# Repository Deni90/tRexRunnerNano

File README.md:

# Welcome to tRexRunnerNano Project

## About
This project tries to be the smallest implementation of Google's easter egg T-Rex Runner with resolution of only 128x32px.

The goal is to make a small game console by using WCH CH32V003 microcontroller and SSSD1306 oled display.

## Schematic  & PCB
Made with KiCAD 10

## Firmware

Firmware is written in C using **ch32fun**, an open source development environment for the CH32V003.

WCH CH-Link is used for flashing the firmware

### Building and flashing

```
make
```

## DM DIY-MORE OLED-091
Popular I2C OLED 32x128 display from diy-more has an issue. It doesn't properly start after power on, but starts without problems after reset.
To solve this problem swap R3 and R4 resistors.

Solution found at:
https://youtu.be/__3InV5tdzM

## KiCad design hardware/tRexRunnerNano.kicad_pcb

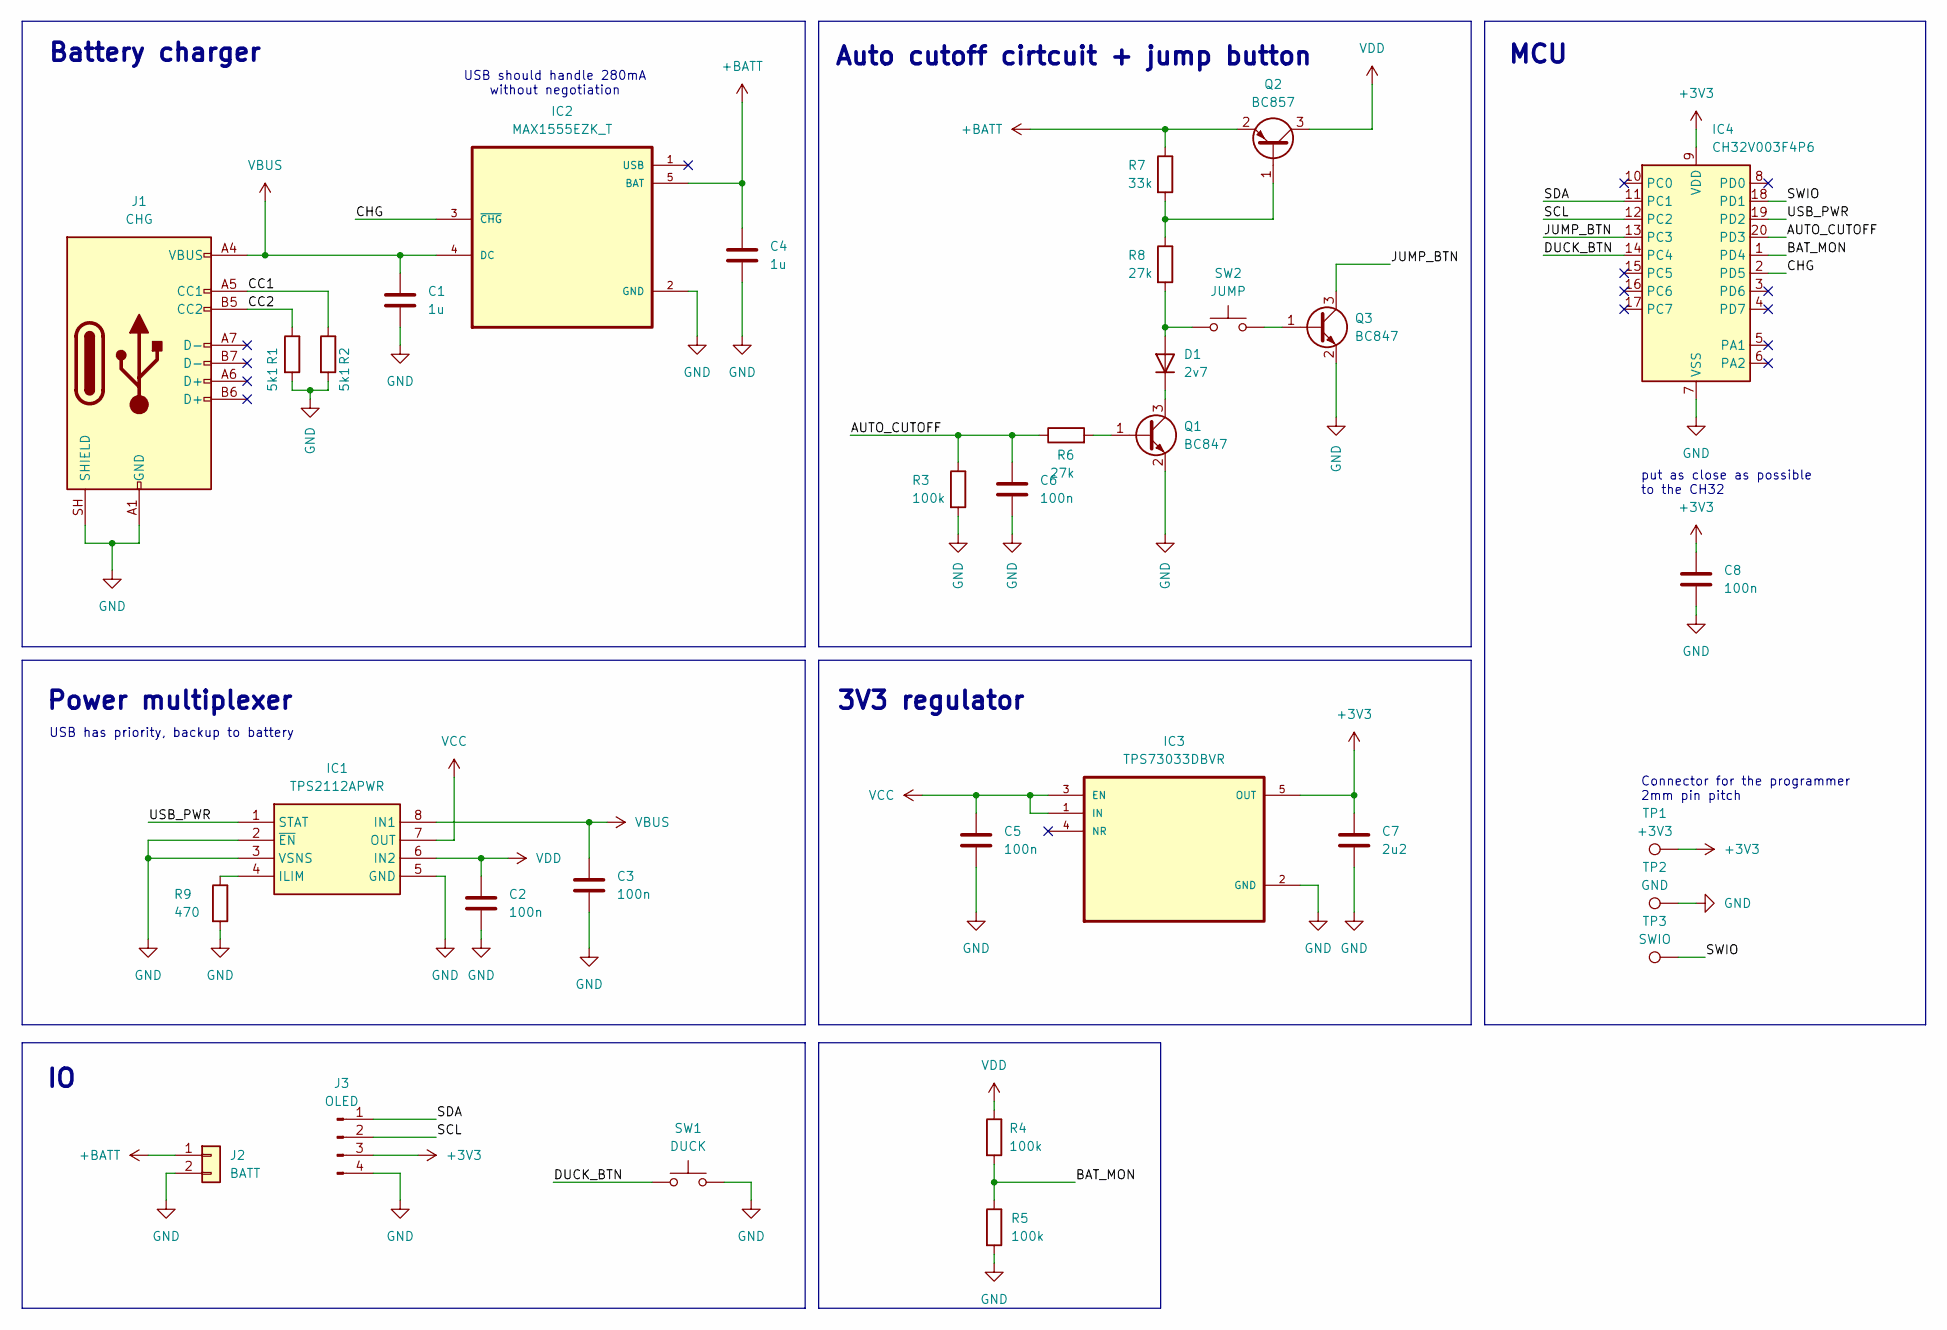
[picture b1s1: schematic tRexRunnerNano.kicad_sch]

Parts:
C1, C4: 1u; C_0603_1608Metric
C2, C3, C5, C6, C8: 100n; C_0603_1608Metric
C7: 2u2; C_0603_1608Metric
D1: 2v7; D_MiniMELF
IC1: TPS2112APWR; SOP65P640X120-8N; Mouser Part Number 595-TPS2112APWR
IC2: MAX1555EZK_T; SOT95P275X110-5N
IC3: TPS73033DBVR; SOT95P280X145-5N
IC4: CH32V003F4P6; TSSOP-20_4.4x6.5mm_P0.65mm
J1: CHG; USB_C_Receptacle_GCT_USB4105-xx-A_16P_TopMnt_Horizontal
J2: BATT; JST_GH_SM02B-GHS-TB_1x02-1MP_P1.25mm_Horizontal
J3: OLED; PinHeader_1x04_P2.54mm_Vertical
Q1, Q3: BC847; SOT-23
Q2: BC857; SOT-23
R1, R2: 5k1; R_0603_1608Metric
R3, R4, R5: 100k; R_0603_1608Metric
R6, R8: 27k; R_0603_1608Metric
R7: 33k; R_0603_1608Metric
R9: 470; R_0603_1608Metric
SW1: DUCK; SW_PUSH_6mm
SW2: JUMP; SW_PUSH_6mm
TP1: +3V3; TestPoint_Pad_D1.0mm
TP2: GND; TestPoint_Pad_D1.0mm
TP3: SWIO; TestPoint_Pad_D1.0mm

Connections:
+3V3: C7.1, C8.1, IC3.5 (OUT), IC4.9 (VDD), J3.3, TP1.1 (1_1)
+BATT: C4.1, IC2.5 (BAT), J2.1, Q2.2 (E), R7.1
/AUTO_CUTOFF: C6.1, IC4.20 (PD3), R3.1, R6.1
/BAT_MON: IC4.1 (PD4), R4.2, R5.1
/CC1: J1.A5 (CC1), R2.1
/CC2: J1.B5 (CC2), R1.1
/CHG: IC2.3 (~CHG), IC4.2 (PD5)
/DUCK_BTN: IC4.14 (PC4), SW1.1
/JUMP_BTN: IC4.13 (PC3), Q3.3 (C)
/SCL: IC4.12 (PC2), J3.2
/SDA: IC4.11 (PC1), J3.1
/SWIO: IC4.18 (PD1), TP3.1 (1_1)
/USB_PWR: IC1.1 (STAT), IC4.19 (PD2)
GND: C1.2, C2.2, C3.2, C4.2, C5.2, C6.2, C7.2, C8.2, IC1.2 (~EN), IC1.3 (VSNS), IC1.5 (GND), IC2.2 (GND), IC3.2 (GND), IC4.7 (VSS), J1.A1 (GND), J1.A12 (GND), J1.B1 (GND), J1.B12 (GND), J1.SH (SHIELD), J2.2, J3.4, Q1.2 (E), Q3.2 (E), R1.2, R2.2, R3.2, R5.2, R9.2, SW1.2, TP2.1 (1_1)
unnamed: D1.2 (A), R8.2, SW2.1
unnamed: D1.1 (K), Q1.3 (C)
unnamed: IC1.4 (ILIM), R9.1
unnamed: Q1.1 (B), R6.2
unnamed: Q2.1 (B), R7.2, R8.1
unnamed: Q3.1 (B), SW2.2
VBUS: C1.1, C3.1, IC1.8 (IN1), IC2.4 (DC), J1.A4 (VBUS), J1.A9 (VBUS), J1.B4 (VBUS), J1.B9 (VBUS)
VCC: C5.1, IC1.7 (OUT), IC3.1 (IN), IC3.3 (EN)
VDD: C2.1, IC1.6 (IN2), Q2.3 (C), R4.1

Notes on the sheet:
Power multiplexer
put as close as possible to the CH32
Connector for the programmer 2mm pin pitch
Battery charger
USB has priority, backup to battery
USB should handle 280mA without negotiation
Auto cutoff cirtcuit + jump button
MCU
3V3 regulator

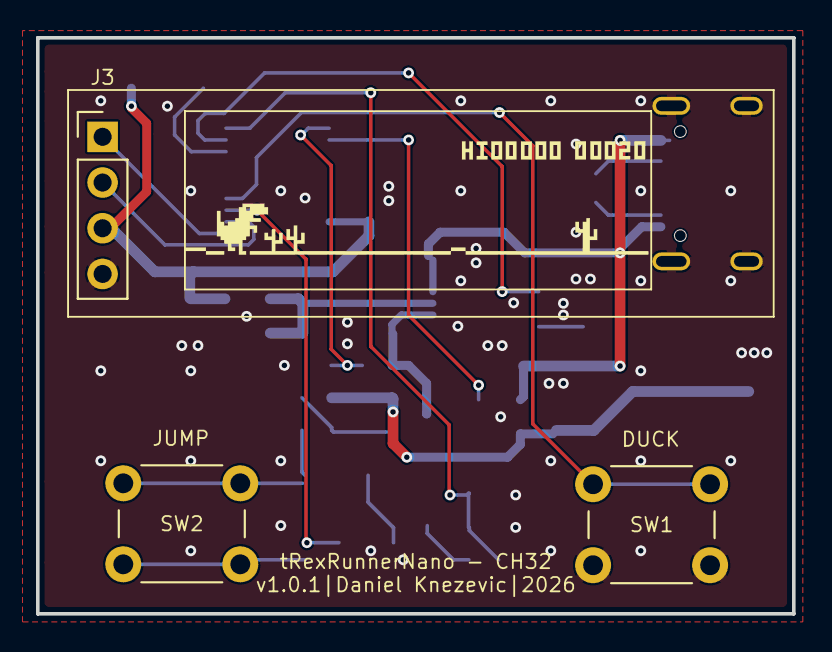
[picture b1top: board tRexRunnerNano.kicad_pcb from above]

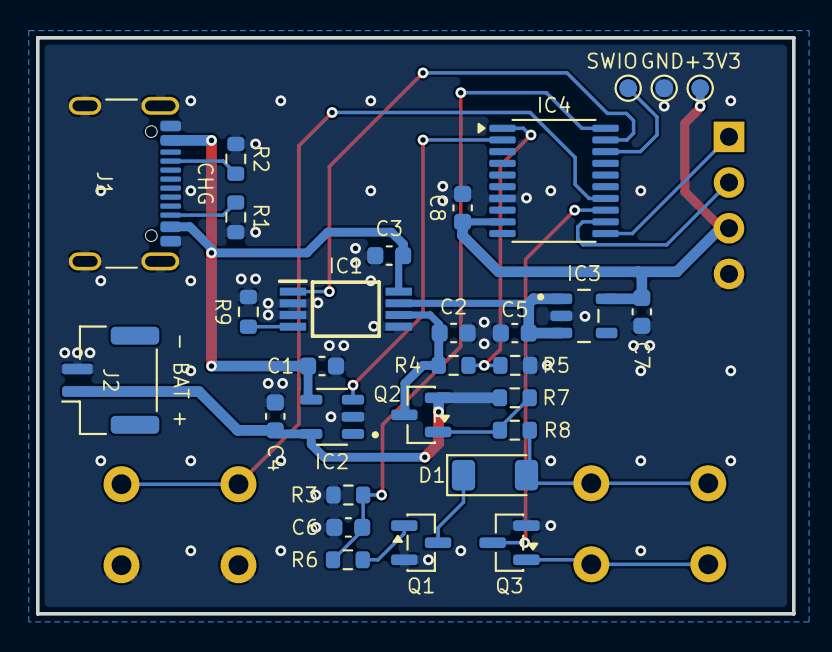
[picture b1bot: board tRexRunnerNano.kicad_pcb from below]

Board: 2 copper layers, 42.0 x 32.0 mm, 33 parts (30 on the bottom side), 23 nets.

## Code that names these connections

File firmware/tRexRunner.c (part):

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#define OLED_STARTUP_DELAY_MS 50

#define JUMP_BUTTON_BIT          0
#define JUMP_BUTTON_GPIO         PC3
#define IS_JUMP_BUTTON_PRESSED() (button_state & (1 << JUMP_BUTTON_BIT))

#define DUCK_BUTTON_BIT          1
#define DUCK_BUTTON_GPIO         PC4
#define IS_DUCK_BUTTON_PRESSED() (button_state & (1 << DUCK_BUTTON_BIT))

#define AUTOCUTOFF_GPIO      PD3
#define CHARGE_COMPLETE_GPIO PD5
#define USB_PWR_GPIO         PD2

#define BOOT_WINDOW_MS      1500
#define STARTUP_INTERVAL_MS 1000
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        boot_window_ms = now_ms;
    }
    uint32_t progress = 0;
    if (!funDigitalRead(USB_PWR_GPIO)) {
        next_state = SYS_BATTERY_CHARGING;
    } else if (IS_JUMP_BUTTON_PRESSED() && IS_DUCK_BUTTON_PRESSED()) {
        // Start holding if we weren't already holding
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        last_icon_update_time_ms = now_ms;
    }
    // Check is the USB still connected. If not, turn off the device
    if (funDigitalRead(USB_PWR_GPIO)) {
        return SYS_SHUTDOWN;
    }
    // Peridically check the battery charge status
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    funDigitalWrite(AUTOCUTOFF_GPIO, FUN_HIGH);
    funPinMode(CHARGE_COMPLETE_GPIO, GPIO_CFGLR_IN_PUPD);
    funDigitalWrite(CHARGE_COMPLETE_GPIO, FUN_HIGH);
    funPinMode(USB_PWR_GPIO, GPIO_CFGLR_IN_PUPD);
    funDigitalWrite(USB_PWR_GPIO, FUN_HIGH);

    // Initializes ADC for battery voltage monitoring
    // code borrowed from ch32fun/examples/adc_polled/adc_polled.c:adc_init()
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    // Enable GPIOD and ADC
    RCC->APB2PCENR |= RCC_APB2Periph_GPIOD | RCC_APB2Periph_ADC1;

    // PD4 is analog input chl 7
    GPIOD->CFGLR &= ~(0xf << (4 * 4));   // CNF = 00: Analog, MODE = 00: Input

    // Reset the ADC to init all regs
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
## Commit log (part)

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2018-07-16 Initializes timer.
2018-07-16 Adds game objects and animations
    - trex animations (running, jumping, ducking)
    - horizon movement
    - flying pterodactyl
    - cactus obstacles
2018-07-17 Adds button handling and miror changes
    - handles buttons
    - updates trex state based on buttons activity
    - changes game parameters
    - adds FB_drawGameObject function
2018-07-17 Fixes formatting game_object definitions
2018-07-18 Adds TODOs
2018-07-18 Refactors button handling
    - button io initialization moved to function
    - created button state monitor
2018-07-18 Moves horizon part to a function
2018-07-18 Moves pterodactyl stuff into function
2018-07-18 Moves trex animations into separate functions
2018-07-18 Adds cactus handling
2018-07-18 Adds cactus and pterodactyl creation
    - extended game_object_t with 'delta'
    - added PNRG initialization
2018-07-19 Adds creation of one more cactus type
2018-07-19 Implements random cactus generation.
2018-07-19 Implements periodic update of game speed
2018-07-23 Renamed FB_functions, replaces button pins with macros
2018-07-23 Implements random pterodactyl generation.
2018-07-23 Implements score and high score.
2018-07-23 Adds clearance between new horizon and trex.
2018-07-23 Adjust game parameters.
2018-07-30 Replaces cactus3 with different design.
2018-07-30 Fixes trex ducking glitch.
2018-07-30 Moves defines with dimensions to source file.
2018-07-31 Fixes dead trex sprite and minor changes.
2018-08-02 Refactoring
    - merges cactuses and pterodactyl into obstacles
    - changes game_objects update functions
    - fixes initialization of cactuses
2018-08-02 Moves sprites into separate header file
2018-08-02 Reimplements horizon drawing
    - creates horizon_t structure
2018-08-02 Implements collision detection
2018-08-02 Implements re(starting) of the game.
    - variables from main() are now global
    - refactored GAME_ funtions
2018-08-02 Tunes game parameters, updates Makefile
    - frame rate dropped to 50FPS
    - MCU frequency set to 8MHz
    - updated MCU fuse bits
2018-08-02 Fixes trex crash into horizon during landing.
2018-08-03 Updates GAME_init and tunes game parameters
    game_speed and trex_state added to GAME_init
2018-08-06 Removes deltas from game_object_t and horizon_t
2018-08-06 Reimplements obstacle generation.
2018-08-06 Changes pterodactyl flying heights.
2018-08-06 Game tuning
2018-08-06 Shows "game over" splash.
2018-08-06 Removes debug print.
2018-08-09 Create LICENSE
2018-08-09 Introduces inverted color mode.
2018-08-09 Fixes trexs jumping height, moves score 1px down.
2018-08-09 Makes variable for avr programmer in Makefile.
2018-08-09 Creates README file
    - adds image folder
2018-09-04 Adds initial hardware desing.
2018-09-05 Changes via sizes.
2018-10-10 Code refactoring by moving it info functions.
    - GAME_AdjustDifficulty: increasing game speed and distance between obstacles
    - GAME_HandleState: switching trex states based on button presses
2018-10-10 Implemented storing high score in eeprom.
2018-10-10 Adds power manager and initializes io pins.
2018-11-19 Fixes read/write from/to eeprom.
2018-11-19 Implements inactivity monitor.
2018-11-19 Implements battery monitoring.
2018-11-20 No need for delay at startup.
    Check README for the solution.
2018-11-20 Removes trex_dead sprite and WAITING state.
2018-11-21 Implements the startup of the device.
    To start the device both buttons should be held for STARTUP_INTERVAL.
    - new function FB_DrawRectangle
    - deleted unused TIMER_delay
2018-11-21 Removes unused functions and refactores code.
    - removed FB_ClearPixel
    - POWER_MANAGER_turnOn and POWER_MANAGER_turnOff converted to macros
    - removed GAME_BackupHighScore and GAME_RestoreHighScore
2018-11-21 Fixes trex jumping height.
2019-01-08 Fixes typo and POWER_MANAGER_ReadBatteryVoltage
2019-01-08 Implement power management (usb & battery charging)
    - created POWER_MANAGER_ShowBatteryStatus for showing battery icon
    - added checking for low battery
    - fixed intialization of CHG_PIN
    - declared TIMER, BUTTON and POWER_MANAGER functions in the header
2019-01-08 Small adjustments of OLED and USB connectors
    - OLED connector has been moved 1mm left
    - micro USB connector has been moved 1mm right
2019-01-08 Schematic: Changes D3 to 2V7
2019-01-16 Decreases gravity to 3.1
2019-01-16 Fixes the horizon when trex is jumping.
2019-01-17 Board: Repositions oled connector, usb and buttons
2019-03-12 Fixes turning off when the init isn't successful
2019-03-12 Fixes Timer1's TOP value for 1mS
2019-03-12 Tunes game parameters and timeout at init.
2019-04-27 Tunes timeout and score inclement values.
2019-04-27 Adds watchdog timer.
2019-04-27 Fixes early start of the game at startup.
2019-04-27 Repositions ssd1306 text on PCB
2019-04-29 Reimplements: Fix for early start of the game at startup.
    - no need for using timer
2019-04-29 Makefile: renames flash_eeprom target to eeprom.
    - updates README file
2019-05-05 Prevents immediate start of the game after gameover
2019-06-25 Implements reseting high score.
2019-06-26 Fizes oled burn while charging battery.
2019-06-26 Fixes bugs when turning off the device.
2019-07-14 Enables BOD at VCC=2V7.
2019-09-16 Enables EESAVE fuse bit to preserve eeprom.
2022-02-06 Adds 3D model for casing
2024-12-17 Port tRexRunner to rpi Pico 2W
2026-05-20 Initial port of firmware to CH32 with new PCB
2026-05-20 Reorganize code
    - Move macros, type definitions, forward declarations to the source file.
    - Make functions static
2026-05-20 Rename button names to match with schematic
2026-05-20 Port POWER_MANAGER to the project
    - Implement ADC init and ADC read functions based on ch32fun examples
2026-05-20 Fix FLASH_Write_u32
    Use code from ch32fun/examples/flashtest/flashtest.c to fix the function
2026-05-21 Port the startup sequence of the game to this repo
2026-05-21 Fix clang-tidy warnings related to braces, types and magic numbers
2026-05-24 Refactor tRexRunner.c to make it more modular and readable.
    - Introduce a state machine representing states of the device
    - Move state implementations to separate functions to make the code more
    readable and maintainable.
    - Handle initialization and factory reset through states removing the need for
    infinite loops.
    - Re-implement BUTTONS_MonitorButtons function to use standard debouncing
2026-05-24 Remove clear function from SSD1306
2026-05-24 PCB: Move vias out out test pads
2026-05-24 Extend state machine with SYS_BATTERY_CHARGING state
    - Rename POWER_MANAGER_ShowBatteryStatus to FB_ShowBatteryStatus
    - Handle battery chargin state in SYS_ProcessBatteryCharging
    - Turn off periodic checks (like buttons, inactivity, ...) while in
    SYS_BATTERY_CHARGING state
